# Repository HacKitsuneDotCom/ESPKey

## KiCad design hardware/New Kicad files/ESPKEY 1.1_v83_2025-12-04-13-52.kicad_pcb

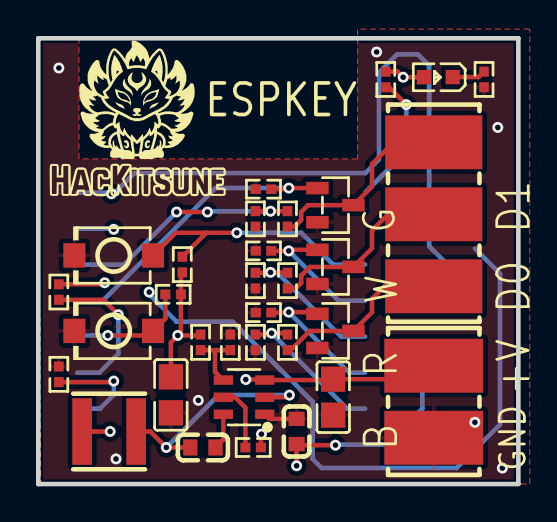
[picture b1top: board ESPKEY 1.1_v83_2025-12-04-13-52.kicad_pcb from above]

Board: 4 copper layers, 26.7 x 24.8 mm, 33 parts (1 on the bottom side), 22 nets.

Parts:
BOOT: SW-SMD_L3.9-W3.0-P4.45
POWER: LED0603-RD_RED
RST: SW-SMD_L3.9-W3.0-P4.45
U1: CONN-SMD_009176002022006
U2: SOT-23-6_L2.9-W1.6-P0.95-LS2.8-BL
U3, U6: C0805
U4, U8, U9, U12, U13, U14, U15, U16, U18, U19, U21, U22, U23, U24, U26, U27, U29, U31: R0402
U5: IND-SMD_L4.0-W4.0_ANR4012
U7, U17: C0603
U11: WIRELM-SMD_ESP-12S
U20, U25, U28: SOT-23-3_L2.9-W1.3-P1.90-LS2.4-BR
U30: CONN-SMD_009176003022006

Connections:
3V3: POWER.2, U5.2, U6.2, U8.2, U11.8, U12.2, U13.2, U15.1, U16.2, U17.2
$1N471: U2.5, U4.2
$1N489: U2.2, U5.1, U7.2
$1N711: U2.6, U7.1
$1N1025: U2.4, U8.1, U9.2
$1N1260: BOOT.1, U11.12, U12.1
$1N1338: U11.11, U13.1
$1N1344: U11.10, U14.1
$1N1485: U11.1, U15.2
$1N1526: RST.1, U11.3, U16.1
$1N3405: POWER.1, U31.2
+5V: U1.1, U2.3, U3.2, U4.1
D0_ASSERT: U11.6, U18.1, U20.1
D0_SENSE: U11.7, U19.2, U21.2
D1_ASSERT: U11.4, U22.1, U25.1
D1_SENSE: U11.5, U23.2, U24.2
GND: BOOT.2, RST.2, U1.2, U2.1, U3.1, U6.1, U9.1, U11.9, U14.2, U17.1, U18.2, U20.2, U21.1, U22.2, U24.1, U25.2, U26.2, U28.2, U29.1, U31.1
LED_ASSERT: U11.13, U26.1, U28.1
LED_SENSE: U11.14, U27.2, U29.2
READER_D0: U19.1, U20.3, U30.3
READER_D1: U23.1, U25.3, U30.2
READER_LED: U27.1, U28.3, U30.1

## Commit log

2025-09-23 Create Original Hardware design files
2026-02-28 Create Original Hardware Design Files
    Original hardware Design Files from octosavvi
2026-03-01 Updated design files

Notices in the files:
hardware/New Kicad files/ESPKEY 1.1_v83_2025-12-04-13-52.kicad_pcb:
by octosavvi (GPLv2)
